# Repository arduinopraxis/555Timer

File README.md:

# 555 Timer
555 Timer Board with THT components

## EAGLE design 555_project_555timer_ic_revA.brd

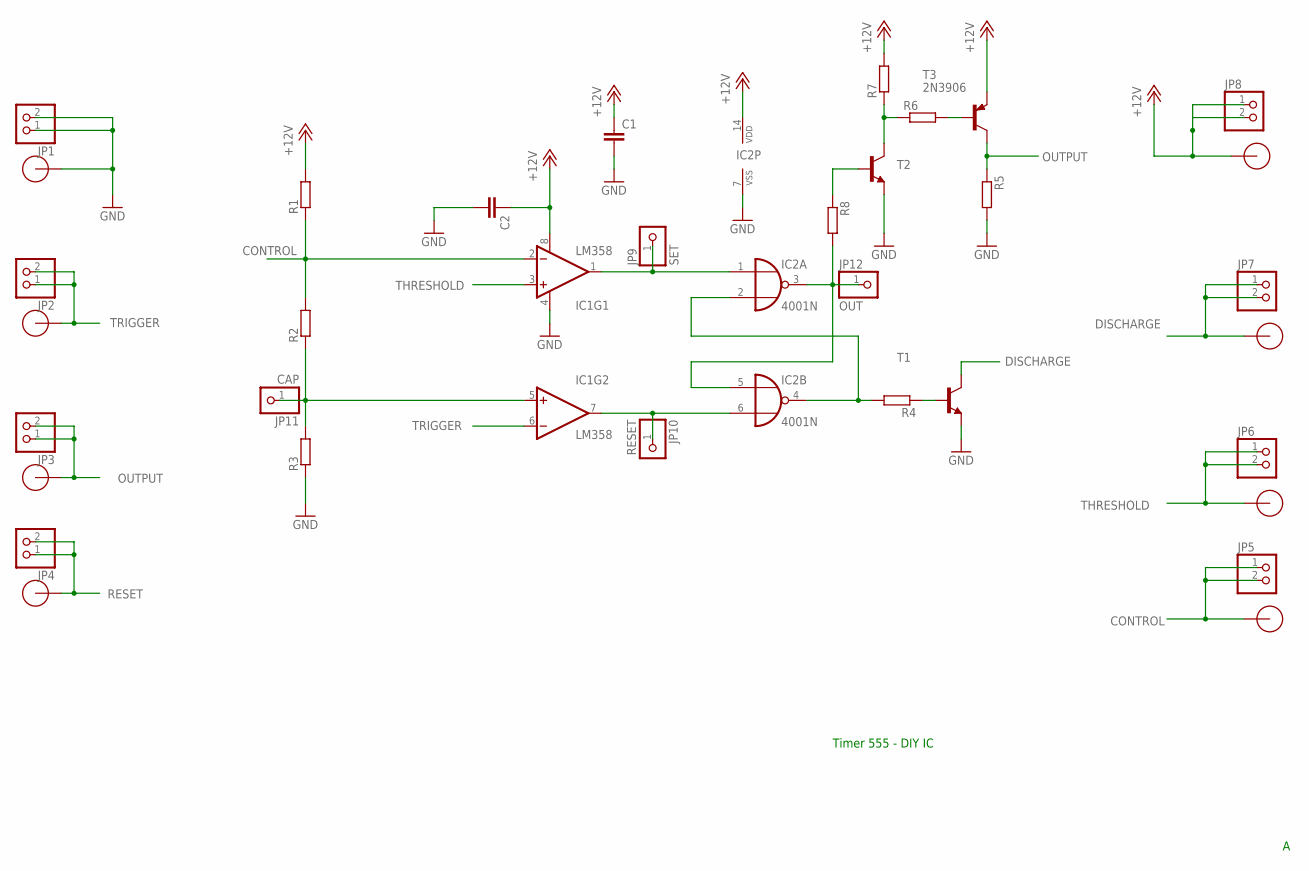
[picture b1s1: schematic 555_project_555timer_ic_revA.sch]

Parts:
C1, C2: C-EU025-024X044; C025-024X044
IC1: LM358; DIP08
IC2: 4001N; DIL14
JP1, JP2, JP3, JP4, JP5, JP6, JP7, JP8: PINHD-1X2; 1X02
JP9: SET; 1X01
JP10: RESET; 1X01
JP11: CAP; 1X01
JP12: OUT; 1X01
R1, R2, R3, R4, R5, R6, R7, R8: R-EU_0204/7; 0204/7
T1: BC546-NPN-TO92-CBE; TO92-CBE
T2: TRANSISTOR_NPN2N3904; TO-92
T3: 2N3906; TO92
U$1, U$3, U$4, U$5, U$6, U$7, U$8, U$9: ALLIGATOR_CLIP_PAD; BIGTAP

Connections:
+12V: C1.1, C2.1, IC1.8 (V+), IC2.14 (VDD), JP8.1, JP8.2, R1.2, R7.2, T3.3 (E), U$7.P$1
CONTROL: IC1.2 (-IN), JP5.1, JP5.2, R1.1, R2.2, U$1.P$1
DISCHARGE: JP7.1, JP7.2, T1.C, U$8.P$1
GND: C1.2, C2.2, IC1.4 (V-), IC2.7 (VSS), JP1.1, JP1.2, R3.1, R5.2, T1.E, T2.1 (E), U$3.P$1
unnamed: IC2.2 (I1), IC2.4 (O), R4.2
unnamed: R4.1, T1.B
unnamed: R8.1, T2.2 (B)
unnamed: IC1.7 (OUT), IC2.6 (I1), JP10.1
unnamed: IC1.5 (+IN), JP11.1, R2.1, R3.2
unnamed: IC1.1 (OUT), IC2.1 (I0), JP9.1
unnamed: R6.1, R7.1, T2.3 (C)
unnamed: R6.2, T3.2 (B)
OUT: IC2.3 (O), IC2.5 (I0), JP12.1, R8.2
OUTPUT: JP3.1, JP3.2, R5.1, T3.1 (C), U$5.P$1
RESET: JP4.1, JP4.2, U$6.P$1
THRESHOLD: IC1.3 (+IN), JP6.1, JP6.2, U$9.P$1
TRIGGER: IC1.6 (-IN), JP2.1, JP2.2, U$4.P$1

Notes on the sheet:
Timer 555 - DIY IC

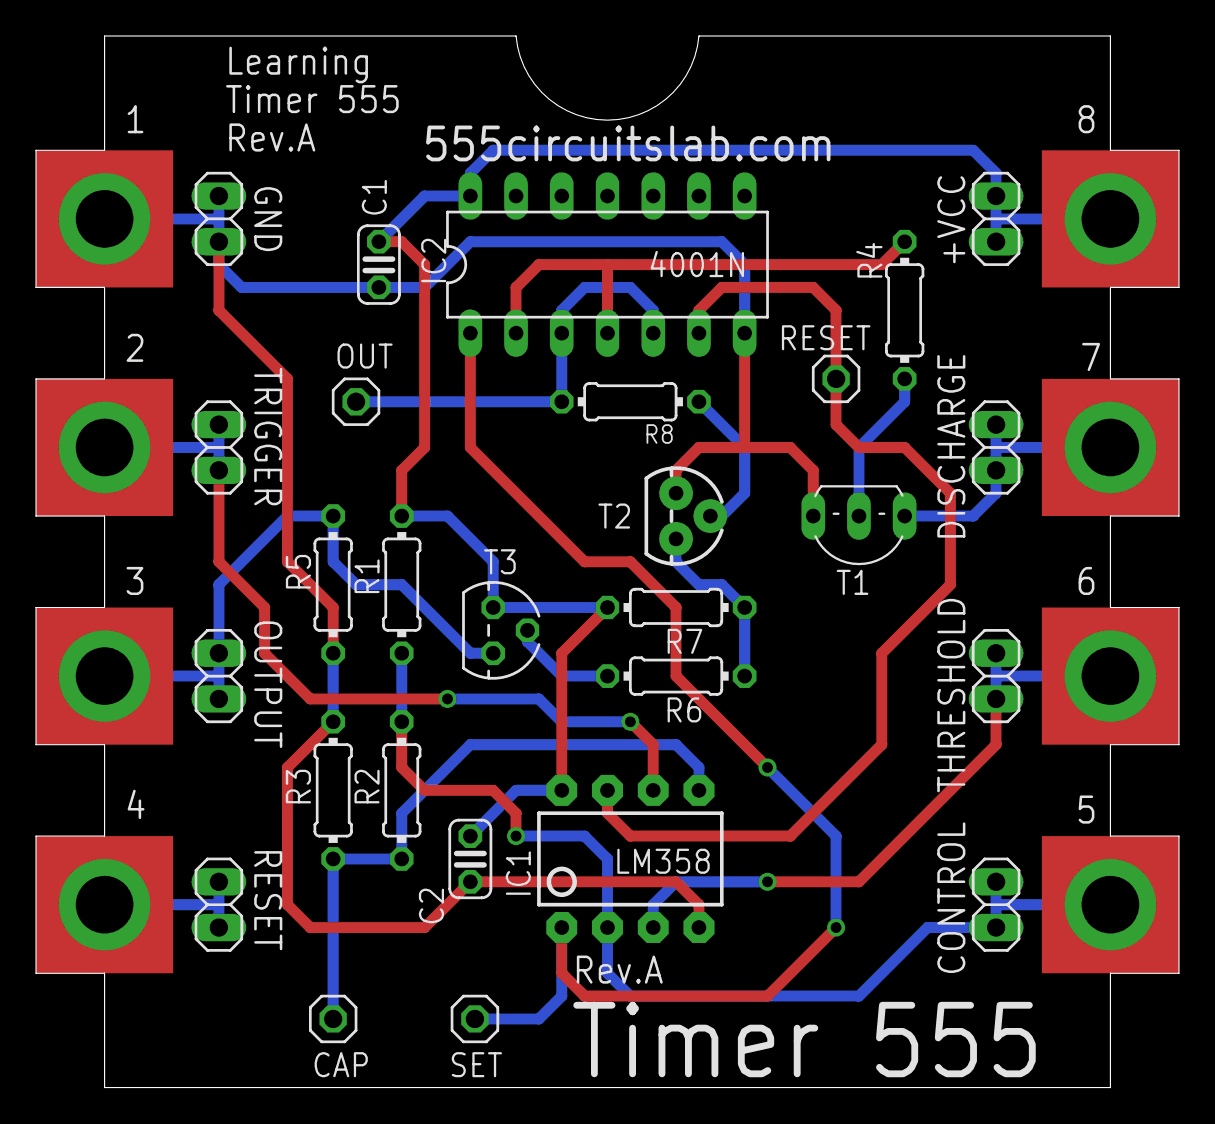
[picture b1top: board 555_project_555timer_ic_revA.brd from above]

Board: 2 copper layers, 63.5 x 58.4 mm, 35 parts (0 on the bottom side), 17 nets.

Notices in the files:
parts and their libraries:
SparkFun-AnalogIC: Licensing:Creative Commons ShareAlike 4.0 International - https://creativecommons.org/licenses/by-sa/4.0
